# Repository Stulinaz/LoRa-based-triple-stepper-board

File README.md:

<!-- For .md file development refers to https://docs.github.com/en -->
# LoRa Wireless Triple Stepper Controller 

## Build for 7th PCBWAy Project Design Contest

[CLICK HERE](https://www.pcbway.com/project/shareproject/LoRa_based_triple_stepper_board_7cf3be2c.html) to see the project.

Designed to remote control up to three axis mechatronic system.
Build with [MIPOT](https://www.mipot.com) [32001506DEU](https://mipot.com/en/products/mip-series/dual-core/32001506deu/) LoRa Open Core module based on 
[STM32WL55JC](https://www.st.com/en/microcontrollers-microprocessors/stm32wl55cc.html) dual core microcontroller.

## Top Side of the board

## Bottom Side of The board

## Board with 4 layers for EMI Compliance

## Build with Kicad

## Main firwmare files for a quick view

## Pcb and stencil order on pcbway

## Mode of Operation

## Closeup

## SPI commonucation between microcontroller and TMC2130 Drivers

## Electrical characteristics

| Parameter                | Description | Min        | Typ     | Max     |  Unit  | Test Conditions         |    
| ---                      |    ---      | ---        | ---     | ---     | ---    | ---                     |   
|**Input Voltage**         | -           | 6          |         | 45      | V      | -                       |   
|**Operating temperature** | -           | 0          | 25      | 55      | \*C    | -                       |
|**Power consumption**     | -           | -          | 47      | -       | mA     | Vcc 6Vdc - Steppers Off |

## Folder content and description

- **technical_docs:** Datasheet, Application notes and manual of the on-board electronic components.
- **firmware:** Source code of the microcontroller written in C.
	- **Core:** The application files, system and peripheral configuration.
	- **freertos:** The Freertos kernel. *Keep read only*.
	- **freertos_cli:** The Freertos command line interface source code. *Keep read only*.
	- **wl-lib:** STM32 HAL and LL Drivers. *Keep read only*.
	- **trinamic_lib:** Driver of TMC2130 stepper controller.
	- **miplib** Driver of MIPOT LoRa Module 32001506DEU. *Keep read only*.
- **img:** Development and test images of the project.
- **kicad:** hardware design files.Source files of schematic and PCB.
	- **lib:** Symbols and footprints of the components.
- **production:** Production files. Gerbers, BOM and Stencil.
- **doc:**  User manual of the board and Schematic. PDF format.

## Bll of materials

Interactive [BOM](https://github.com/Stulinaz/LoRa-based-triple-stepper-board/blob/master/production/ibom.html).

## Firmware characteristics

Based on [Freertos](https://www.freertos.org) with simple and clean development.
.

## Software needed for development

- [STM32CubeIDE](https://www.st.com/en/development-tools/stm32cubeide.html) **1.17.0**
- [KICAD](https://www.kicad.org/) **8.0.5**
- [GIT](https://git-scm.com/) **2.46.1.windows.1**
- [Tera Term](https://teratermproject.github.io/index-en.html) **5.3 x86**

## Tools needed for development

Programmer [STLINK](https://www.st.com/en/development-tools/st-link-v2.html).

## License

Shown in the LICENSE.md file

## Developers

Hardware developer: [@ts-manuel](https://github.com/ts-manuel)
Firmware developer: [@Stulinaz](https://github.com/Stulinaz)

> [!CAUTION]
> Manual soldering of SMD components requires high level of manual skills.
> Project not suited for beginners in firmware development.
> A good understanding of C language is a must.

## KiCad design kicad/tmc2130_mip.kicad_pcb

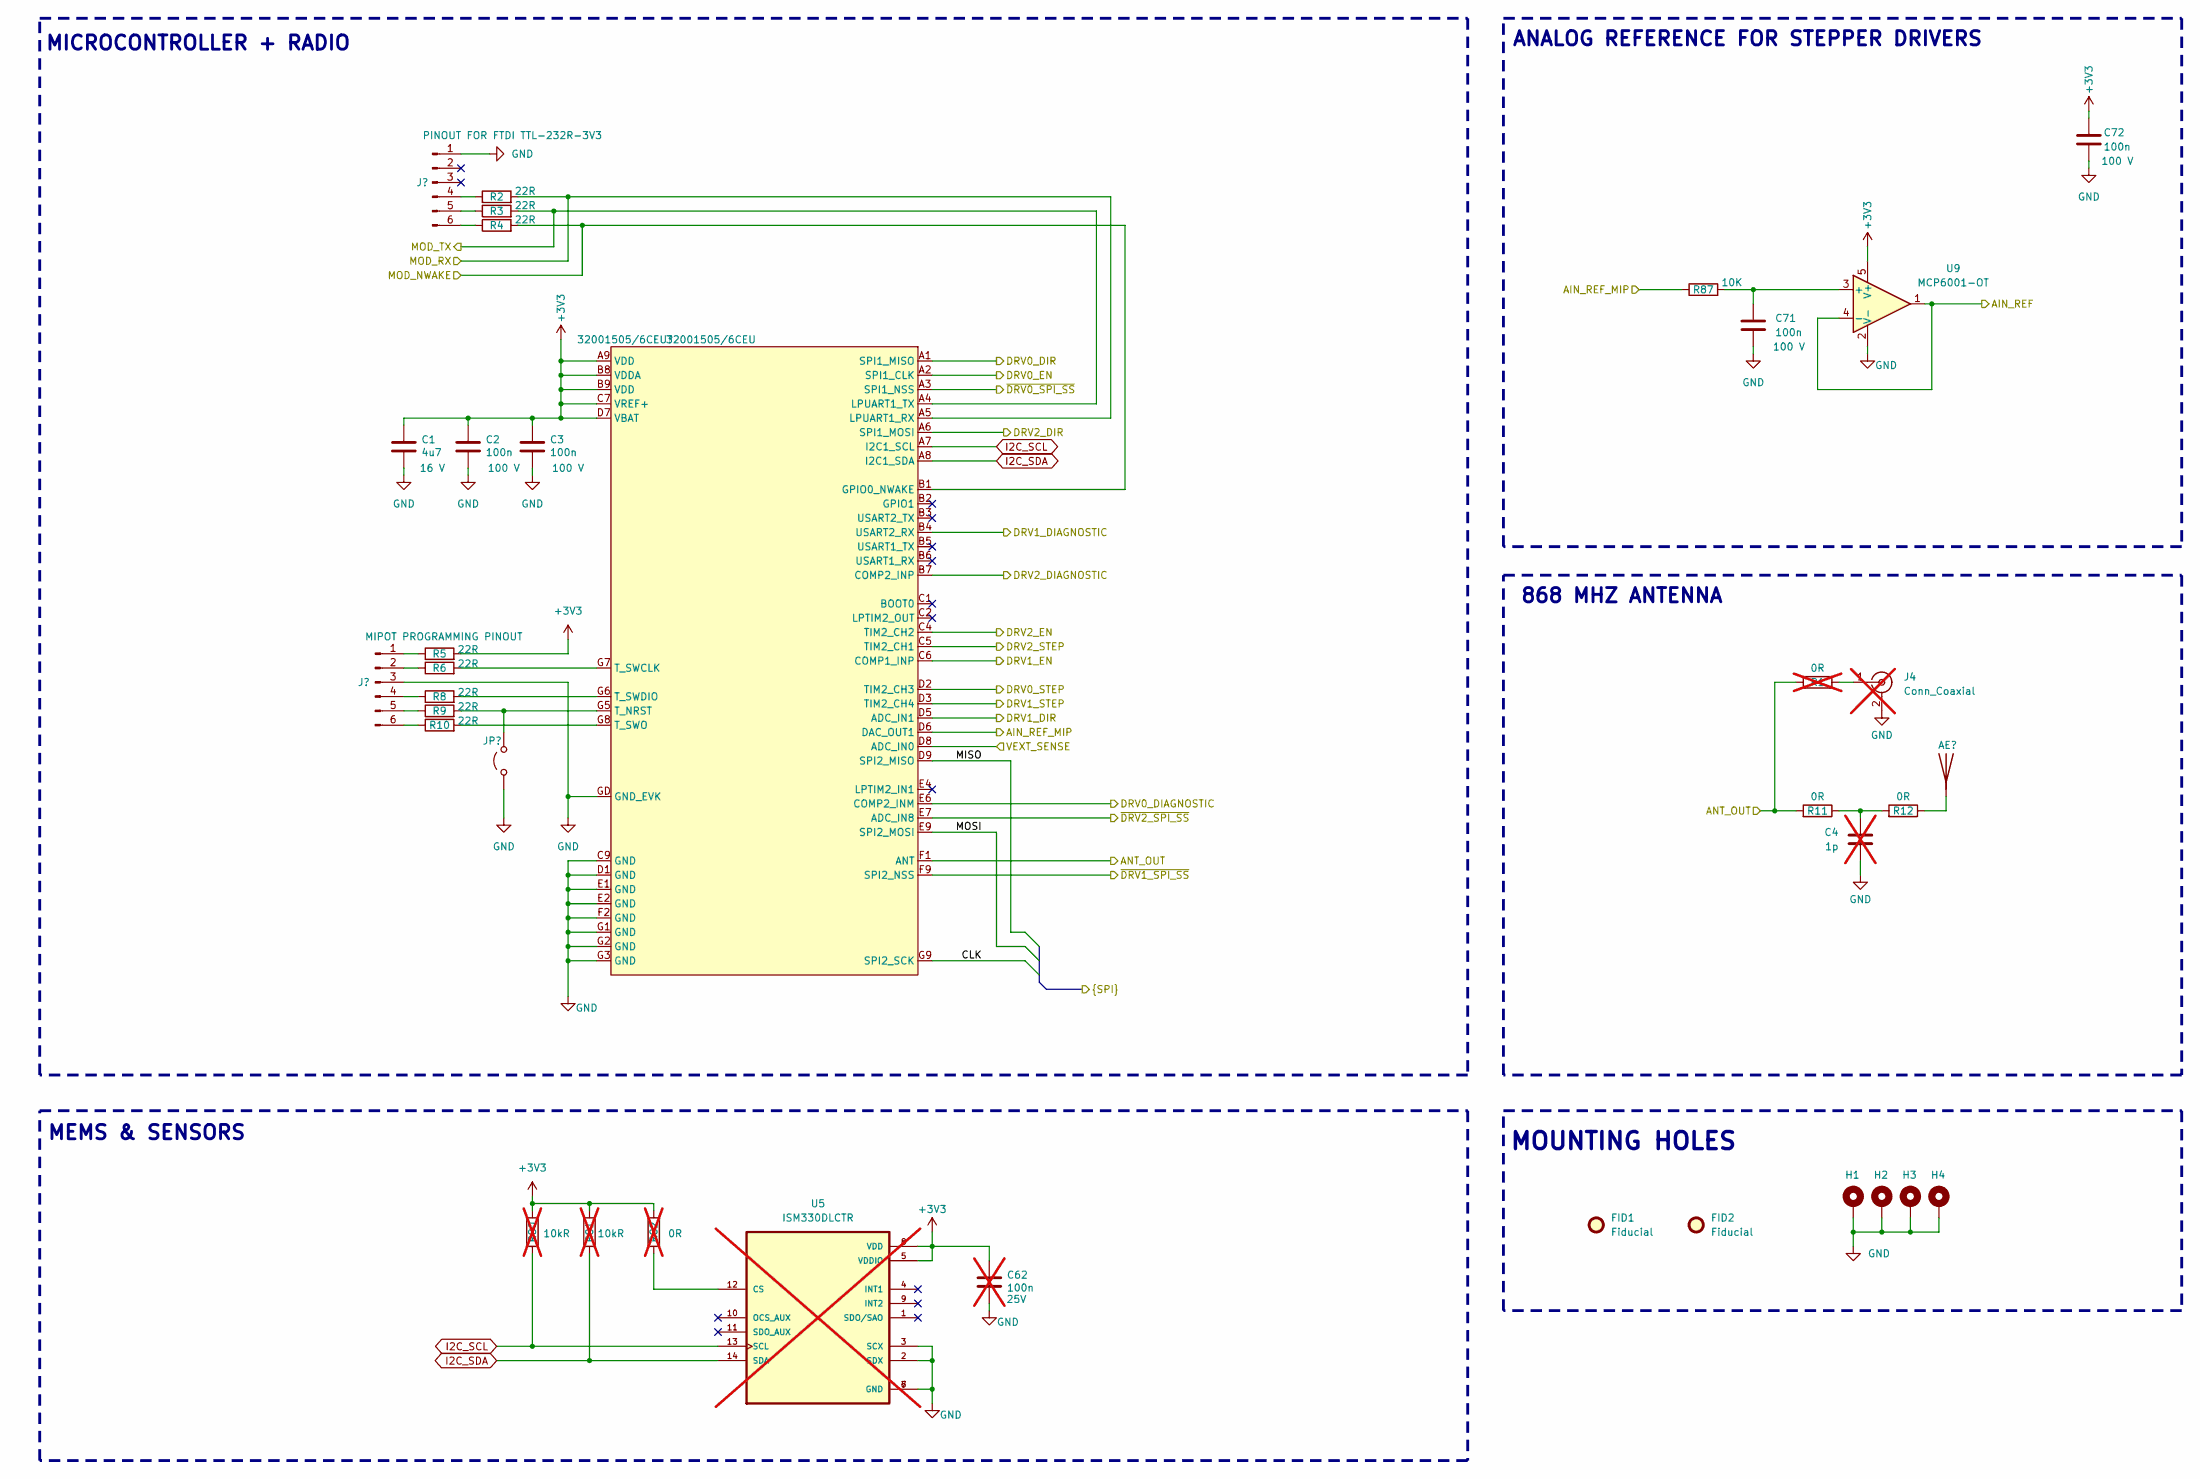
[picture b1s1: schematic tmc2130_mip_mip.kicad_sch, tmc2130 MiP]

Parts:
AE1: Antenna; Texas_SWRA416_868MHz_915MHz
C1: 4u7; C_0805_2012Metric_Pad1.18x1.45mm_HandSolder; Voltage 16 V; Mouser 81-GRM21BR71C475KE1L
C2, C3, C71, C72: 100n; C_0603_1608Metric_Pad1.08x0.95mm_HandSolder; Voltage 100 V; Mouser 187-CL10B104KC8NNNC
C4: 1p; C_0603_1608Metric_Pad1.08x0.95mm_HandSolder; not fitted
C62: 100n; C_0603_1608Metric_Pad1.08x0.95mm_HandSolder; not fitted
FID1, FID2: Fiducial; Fiducial_2.0mm_Mask4.0mm
H1, H2, H3, H4: MountingHole_Pad; MountingHole_4.3mm_M4_ISO7380_Pad_TopBottom
J1: Conn_01x06_Pin; PinSocket_1x06_P2.54mm_Vertical
J2: Conn_01x06_Pin; PinHeader_1x06_P2.54mm_Vertical
J4: Conn_Coaxial; U.FL_Molex_MCRF_73412-0110_Vertical; Mouser 538-73412-0110; not fitted
JP1: Jumper_2_Open; PinHeader_1x02_P2.54mm_Vertical
M1: 32001505/6CEU; 32001514_R2
R1, R82: 0R; R_0603_1608Metric_Pad0.98x0.95mm_HandSolder; not fitted
R2, R3, R4, R5, R6, R8, R9, R10: 22R; R_0603_1608Metric_Pad0.98x0.95mm_HandSolder; Mouser 603-AC0603JR-0722RL
R11, R12: 0R; R_0603_1608Metric_Pad0.98x0.95mm_HandSolder; Mouser 603-RC0603FR-100RL
R80, R81: 10kR; R_0603_1608Metric_Pad0.98x0.95mm_HandSolder; not fitted
R87: 10K; R_0603_1608Metric_Pad0.98x0.95mm_HandSolder; Mouser 603-RC0603JR-0710KL
U5: ISM330DLCTR; PQFN50P250X300X86-14N; PARTREV 2; not fitted
U9: MCP6001-OT; SOT-23-5; Mouser 579-MCP6001T-E/OT

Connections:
+3V3: C1.2, C2.2, C3.2, C62.2, C72.2, M1.A9 (VDD), M1.B8 (VDDA), M1.B9 (VDD), M1.C7 (VREF+), M1.D7 (VBAT), R5.2, R80.1, R81.1, R82.1, U5.5 (VDDIO), U5.8 (VDD), U9.5 (V+); also elsewhere on the board
/CPU/AIN_REF: U9.1, U9.4 (-); also elsewhere on the board
/CPU/AIN_REF_MIP: M1.D6 (DAC_OUT1), R87.1
/CPU/ANT_OUT: M1.F1 (ANT), R1.2, R11.2
/CPU/CLK: M1.G9 (SPI2_SCK); also elsewhere on the board
/CPU/DRV0_DIAGNOSTIC: M1.E6 (COMP2_INM); also elsewhere on the board
/CPU/DRV0_DIR: M1.A1 (SPI1_MISO); also elsewhere on the board
/CPU/DRV0_EN: M1.A2 (SPI1_CLK); also elsewhere on the board
/CPU/DRV0_STEP: M1.D2 (TIM2_CH3); also elsewhere on the board
/CPU/DRV1_DIAGNOSTIC: M1.B4 (USART2_RX); also elsewhere on the board
/CPU/DRV1_DIR: M1.D5 (ADC_IN1); also elsewhere on the board
/CPU/DRV1_EN: M1.C6 (COMP1_INP); also elsewhere on the board
/CPU/DRV1_STEP: M1.D3 (TIM2_CH4); also elsewhere on the board
/CPU/DRV2_DIAGNOSTIC: M1.B7 (COMP2_INP); also elsewhere on the board
/CPU/DRV2_DIR: M1.A6 (SPI1_MOSI); also elsewhere on the board
/CPU/DRV2_EN: M1.C4 (TIM2_CH2); also elsewhere on the board
/CPU/DRV2_STEP: M1.C5 (TIM2_CH1); also elsewhere on the board
/CPU/MISO: M1.D9 (SPI2_MISO); also elsewhere on the board
/CPU/MOD_NWAKE: M1.B1 (GPIO0_NWAKE), R4.2; also elsewhere on the board
/CPU/MOD_RX: M1.A5 (LPUART1_RX), R2.2; also elsewhere on the board
/CPU/MOD_TX: M1.A4 (LPUART1_TX), R3.2; also elsewhere on the board
/CPU/MOSI: M1.E9 (SPI2_MOSI); also elsewhere on the board
/CPU/VEXT_SENSE: M1.D8 (ADC_IN0); also elsewhere on the board
/CPU/~DRV0_SPI_SS: M1.A3 (SPI1_NSS); also elsewhere on the board
/CPU/~DRV1_SPI_SS: M1.F9 (SPI2_NSS); also elsewhere on the board
/CPU/~DRV2_SPI_SS: M1.E7 (ADC_IN8); also elsewhere on the board
GND: C1.1, C2.1, C3.1, C4.1, C62.1, C71.1, C72.1, H1.1, H2.1, H3.1, H4.1, J1.1, J2.3, J4.2 (Ext), JP1.1 (A), M1.C9 (GND), M1.D1 (GND), M1.E1 (GND), M1.E2 (GND), M1.F2 (GND), M1.G1 (GND), M1.G2 (GND), M1.G3 (GND), M1.GD (GND_EVK), U5.2 (SDX), U5.3 (SCX), U5.6 (GND), U5.7 (GND), U9.2 (V-); also elsewhere on the board
I2C_SCL: M1.A7 (I2C1_SCL), R80.2, U5.13 (SCL)
I2C_SDA: M1.A8 (I2C1_SDA), R81.2, U5.14 (SDA)
unnamed: AE1.1 (A), R12.1
unnamed: C4.2, R11.1, R12.2
unnamed: J1.4, R2.1
unnamed: J1.5, R3.1
unnamed: J1.6, R4.1
unnamed: J2.1, R5.1
unnamed: J2.2, R6.1
unnamed: J2.4, R8.1
unnamed: J2.5, R9.1
unnamed: J2.6, R10.1
unnamed: J4.1 (In), R1.1
unnamed: JP1.2 (B), M1.G5 (T_NRST), R9.2
unnamed: M1.G7 (T_SWCLK), R6.2
unnamed: M1.G6 (T_SWDIO), R8.2
unnamed: M1.G8 (T_SWO), R10.2
unnamed: R82.2, U5.12 (CS)
unnamed: C71.2, R87.2, U9.3 (+)

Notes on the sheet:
MEMS & SENSORS
MICROCONTROLLER + RADIO
MOUNTING HOLES
ANALOG REFERENCE FOR STEPPER DRIVERS
868 MHZ ANTENNA

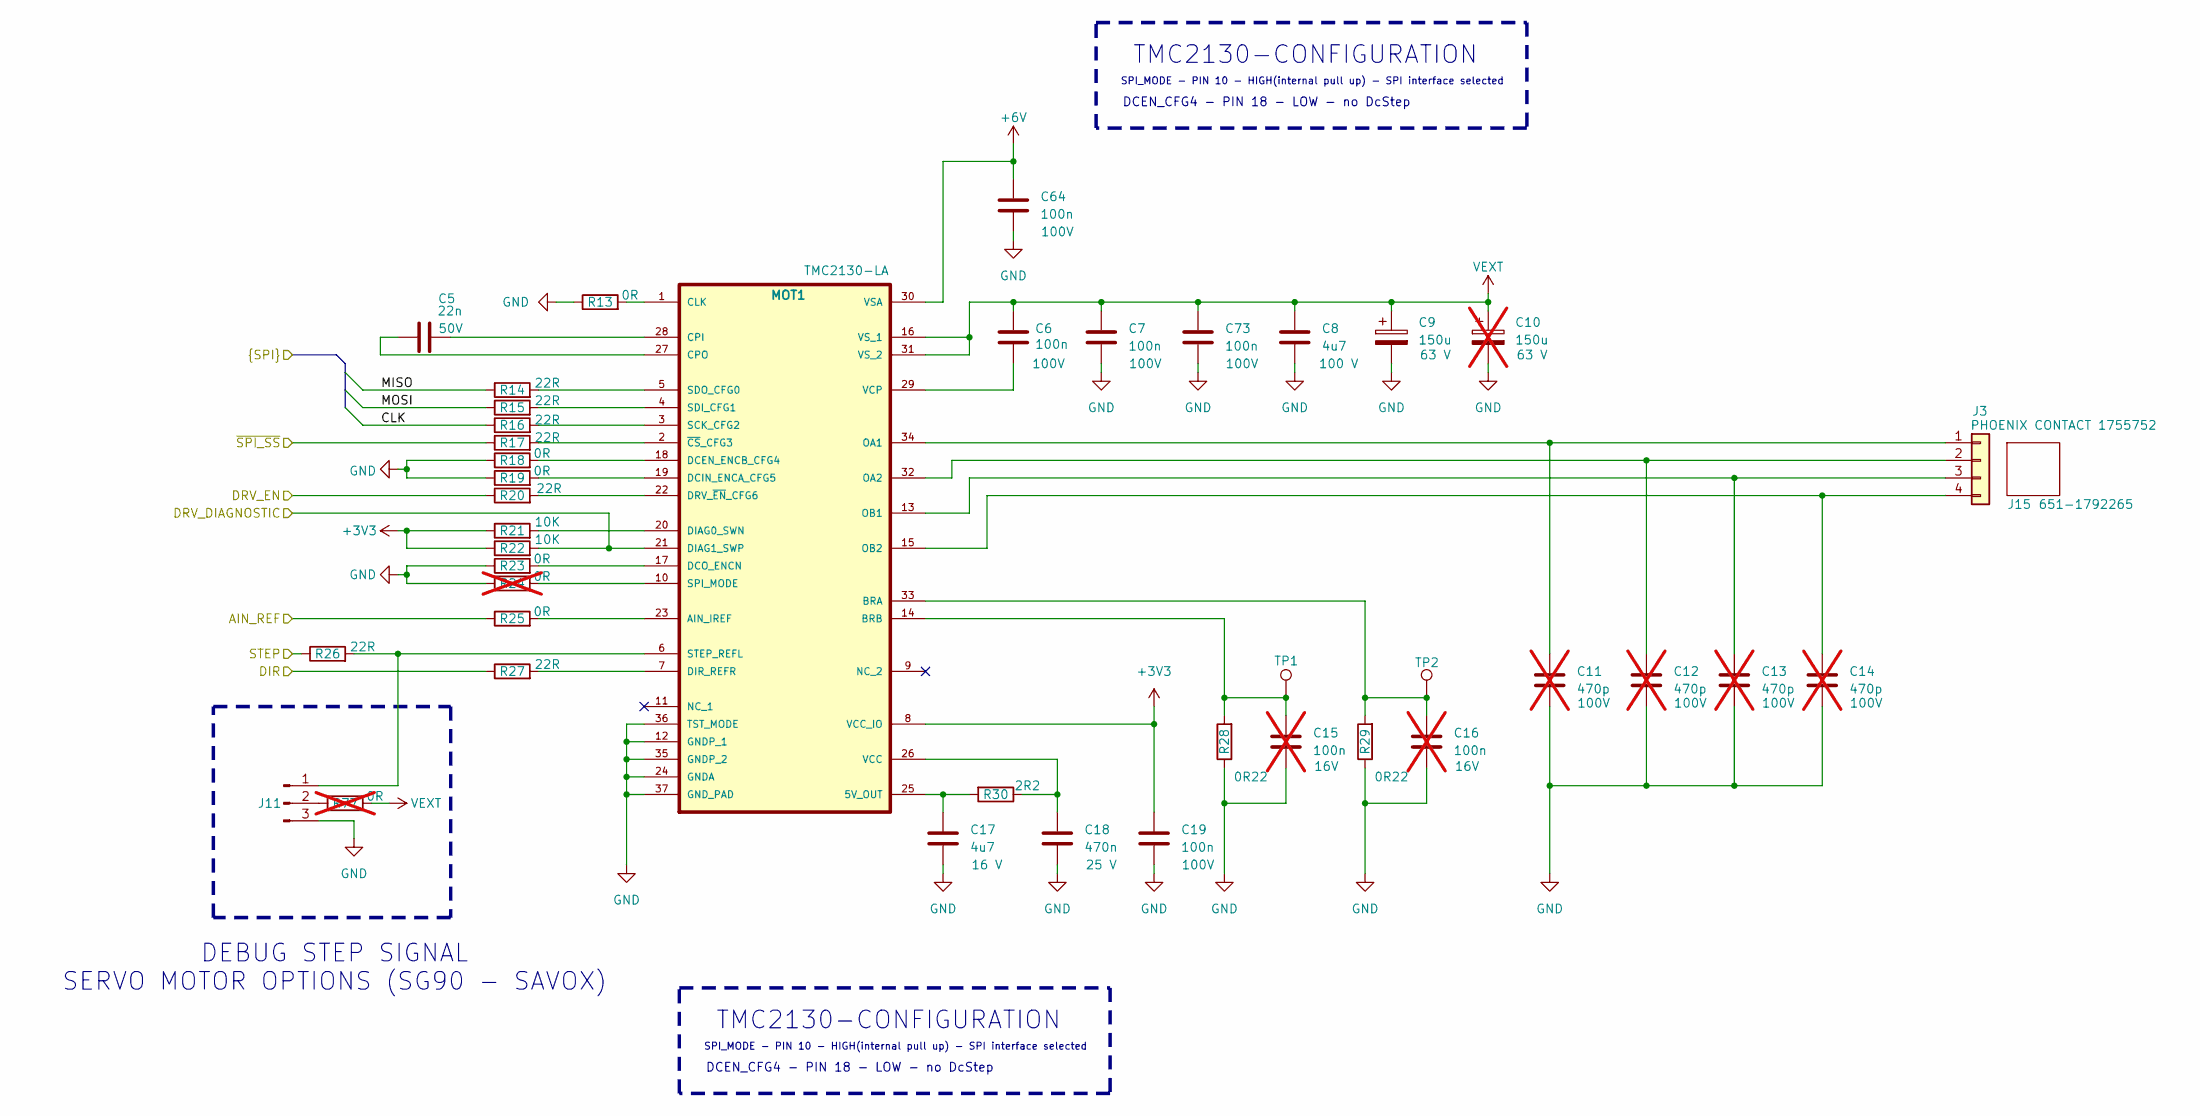
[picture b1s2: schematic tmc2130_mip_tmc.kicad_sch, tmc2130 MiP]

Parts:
C5: 22n; C_0603_1608Metric_Pad1.08x0.95mm_HandSolder; Voltage 50V; Mouser 810-C1608X7R1H223K
C6, C7, C19, C64, C73: 100n; C_0603_1608Metric_Pad1.08x0.95mm_HandSolder; Voltage 100V; Mouser 187-CL10B104KC8NNNC
C8: 4u7; C_1206_3216Metric_Pad1.33x1.80mm_HandSolder; Voltage 100 V; Mouser 81-GRM31CZ72A475K11L
C9: 150u; CP_Radial_D10.0mm_P5.00mm; Voltage 63 V; Mouser 667-EEU-FR1J151
C10: 150u; CP_Radial_D10.0mm_P5.00mm; Voltage 63 V; Mouser 667-EEU-FR1J151; not fitted
C11, C12, C13, C14: 470p; C_0603_1608Metric_Pad1.08x0.95mm_HandSolder; not fitted
C15, C16: 100n; C_0603_1608Metric_Pad1.08x0.95mm_HandSolder; Voltage 100 V; Mouser 187-CL10B104KC8NNNC; not fitted
C17: 4u7; C_0805_2012Metric_Pad1.18x1.45mm_HandSolder; Voltage 16 V; Mouser 81-GRM21BR71C475KE1L
C18: 470n; C_0603_1608Metric_Pad1.08x0.95mm_HandSolder; Voltage 25 V; Mouser 187-CL10B474KA8NNNC
J3: PHOENIX CONTACT 1755752; PHOENIX_1755752; Mouser 651-1755752
J11: Conn_01x03_Pin; PinHeader_1x03_P2.54mm_Vertical
J15: PHOENIX_MVSTBR 2,5 4-ST-5,08; Mouser 651-1792265
MOT1: TMC2130-LA; TMC_QFN36_0.5_5.0X6.0; Mouser 700-TMC2130LA
R13, R18, R19, R23, R25: 0R; R_0603_1608Metric_Pad0.98x0.95mm_HandSolder; Mouser 603-RC0603FR-100RL
R14, R15, R16, R17, R20, R26, R27: 22R; R_0603_1608Metric_Pad0.98x0.95mm_HandSolder; Mouser 603-AC0603JR-0722RL
R21, R22: 10K; R_0603_1608Metric_Pad0.98x0.95mm_HandSolder; Mouser 603-RC0603JR-0710KL
R24, R77: 0R; R_0603_1608Metric_Pad0.98x0.95mm_HandSolder; not fitted
R28, R29: 0R22; R_1206_3216Metric_Pad1.30x1.75mm_HandSolder; Mouser 603-RL1206FR070R22L
R30: 2R2; R_0603_1608Metric_Pad0.98x0.95mm_HandSolder; Mouser 603-RC0603JR-072R2L
TP1, TP2: TestPoint; TestPoint_Pad_D1.0mm

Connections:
+3V3: C19.2, MOT1.8 (VCC_IO), R21.1, R22.1; also elsewhere on the board
+6V: C64.2, MOT1.30 (VSA); also elsewhere on the board
/CPU/AIN_REF: R25.1; also elsewhere on the board
/CPU/CLK: R16.1; also elsewhere on the board
/CPU/DRV0_DIAGNOSTIC: MOT1.21 (DIAG1_SWP), R22.2; also elsewhere on the board
/CPU/DRV0_DIR: R27.1; also elsewhere on the board
/CPU/DRV0_EN: R20.1; also elsewhere on the board
/CPU/DRV0_STEP: R26.1; also elsewhere on the board
/CPU/MISO: R14.1; also elsewhere on the board
/CPU/MOSI: R15.1; also elsewhere on the board
/CPU/~DRV0_SPI_SS: R17.1; also elsewhere on the board
GND: C7.1, C8.1, C9.2, C10.2, C11.2, C12.2, C13.2, C14.2, C15.1, C16.1, C17.1, C18.1, C19.1, C64.1, C73.1, J11.3, MOT1.12 (GNDP_1), MOT1.24 (GNDA), MOT1.35 (GNDP_2), MOT1.36 (TST_MODE), MOT1.37 (GND_PAD), R13.1, R18.1, R19.1, R23.1, R24.1, R28.1, R29.1; also elsewhere on the board
unnamed: C11.1, J3.1, MOT1.34 (OA1)
unnamed: C12.1, J3.2, MOT1.32 (OA2)
unnamed: C13.1, J3.3, MOT1.13 (OB1)
unnamed: C14.1, J3.4, MOT1.15 (OB2)
unnamed: J11.1, MOT1.6 (STEP_REFL), R26.2
unnamed: J11.2, R77.1
unnamed: C17.2, MOT1.25 (5V_OUT), R30.2
unnamed: MOT1.23 (AIN_IREF), R25.2
unnamed: C16.2, MOT1.33 (BRA), R29.2, TP2.1
unnamed: C15.2, MOT1.14 (BRB), R28.2, TP1.1
unnamed: MOT1.1 (CLK), R13.2
unnamed: C5.1, MOT1.28 (CPI)
unnamed: C5.2, MOT1.27 (CPO)
unnamed: MOT1.18 (DCEN_ENCB_CFG4), R18.2
unnamed: MOT1.19 (DCIN_ENCA_CFG5), R19.2
unnamed: MOT1.17 (DCO_ENCN), R23.2
unnamed: MOT1.20 (DIAG0_SWN), R21.2
unnamed: MOT1.7 (DIR_REFR), R27.2
unnamed: MOT1.22 (DRV_~EN_CFG6), R20.2
unnamed: MOT1.3 (SCK_CFG2), R16.2
unnamed: MOT1.4 (SDI_CFG1), R15.2
unnamed: MOT1.5 (SDO_CFG0), R14.2
unnamed: MOT1.10 (SPI_MODE), R24.2
unnamed: C18.2, MOT1.26 (VCC), R30.1
unnamed: C6.1, MOT1.29 (VCP)
unnamed: MOT1.2 (~CS_CFG3), R17.2
VEXT: C6.2, C7.2, C8.2, C9.1, C10.1, C73.2, MOT1.16 (VS_1), MOT1.31 (VS_2), R77.2; also elsewhere on the board

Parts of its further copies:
C20, C35: 22n; C_0603_1608Metric_Pad1.08x0.95mm_HandSolder; Voltage 50V; Mouser 810-C1608X7R1H223K
C21, C22, C34, C36, C37, C49, C68, C69, C74, C75: 100n; C_0603_1608Metric_Pad1.08x0.95mm_HandSolder; Voltage 100V; Mouser 187-CL10B104KC8NNNC
C23, C38: 4u7; C_1206_3216Metric_Pad1.33x1.80mm_HandSolder; Voltage 100 V; Mouser 81-GRM31CZ72A475K11L
C24, C39: 150u; CP_Radial_D10.0mm_P5.00mm; Voltage 63 V; Mouser 667-EEU-FR1J151
C25, C40: 150u; CP_Radial_D10.0mm_P5.00mm; Voltage 63 V; Mouser 667-EEU-FR1J151; not fitted
C26, C27, C28, C29, C41, C42, C43, C44: 470p; C_0603_1608Metric_Pad1.08x0.95mm_HandSolder; not fitted
C30, C31, C45, C46: 100n; C_0603_1608Metric_Pad1.08x0.95mm_HandSolder; Voltage 100 V; Mouser 187-CL10B104KC8NNNC; not fitted
C32, C47: 4u7; C_0805_2012Metric_Pad1.18x1.45mm_HandSolder; Voltage 16 V; Mouser 81-GRM21BR71C475KE1L
C33, C48: 470n; C_0603_1608Metric_Pad1.08x0.95mm_HandSolder; Voltage 25 V; Mouser 187-CL10B474KA8NNNC
J5, J7: PHOENIX CONTACT 1755752; PHOENIX_1755752; Mouser 651-1755752
J12, J13: Conn_01x03_Pin; PinHeader_1x03_P2.54mm_Vertical
J16, J17: PHOENIX_MVSTBR 2,5 4-ST-5,08; Mouser 651-1792265
MOT2, MOT3: TMC2130-LA; TMC_QFN36_0.5_5.0X6.0; Mouser 700-TMC2130LA
R31, R36, R37, R41, R43, R49, R54, R55, R59, R61: 0R; R_0603_1608Metric_Pad0.98x0.95mm_HandSolder; Mouser 603-RC0603FR-100RL
R32, R33, R34, R35, R38, R44, R45, R50, R51, R52, R53, R56, R62, R63: 22R; R_0603_1608Metric_Pad0.98x0.95mm_HandSolder; Mouser 603-AC0603JR-0722RL
R39, R40, R57, R58: 10K; R_0603_1608Metric_Pad0.98x0.95mm_HandSolder; Mouser 603-RC0603JR-0710KL
R42, R60, R78, R79: 0R; R_0603_1608Metric_Pad0.98x0.95mm_HandSolder; not fitted
R46, R47, R64, R65: 0R22; R_1206_3216Metric_Pad1.30x1.75mm_HandSolder; Mouser 603-RL1206FR070R22L
R48, R66: 2R2; R_0603_1608Metric_Pad0.98x0.95mm_HandSolder; Mouser 603-RC0603JR-072R2L
TP3, TP4, TP5, TP6: TestPoint; TestPoint_Pad_D1.0mm

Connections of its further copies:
+3V3: C34.2, C49.2, MOT2.8 (VCC_IO), MOT3.8 (VCC_IO), R39.1, R40.1, R57.1, R58.1; also elsewhere on the board
+6V: C68.2, C69.2, MOT2.30 (VSA), MOT3.30 (VSA); also elsewhere on the board
/CPU/AIN_REF: R43.1, R61.1; also elsewhere on the board
/CPU/CLK: R34.1, R52.1; also elsewhere on the board
/CPU/DRV1_DIAGNOSTIC: MOT2.21 (DIAG1_SWP), R40.2; also elsewhere on the board
/CPU/DRV1_DIR: R45.1; also elsewhere on the board
/CPU/DRV1_EN: R38.1; also elsewhere on the board
/CPU/DRV1_STEP: R44.1; also elsewhere on the board
/CPU/DRV2_DIAGNOSTIC: MOT3.21 (DIAG1_SWP), R58.2; also elsewhere on the board
/CPU/DRV2_DIR: R63.1; also elsewhere on the board
/CPU/DRV2_EN: R56.1; also elsewhere on the board
/CPU/DRV2_STEP: R62.1; also elsewhere on the board
/CPU/MISO: R32.1, R50.1; also elsewhere on the board
/CPU/MOSI: R33.1, R51.1; also elsewhere on the board
/CPU/~DRV1_SPI_SS: R35.1; also elsewhere on the board
/CPU/~DRV2_SPI_SS: R53.1; also elsewhere on the board
GND: C22.1, C23.1, C24.2, C25.2, C26.2, C27.2, C28.2, C29.2, C30.1, C31.1, C32.1, C33.1, C34.1, C37.1, C38.1, C39.2, C40.2, C41.2, C42.2, C43.2, C44.2, C45.1, C46.1, C47.1, C48.1, C49.1, C68.1, C69.1, C74.1, C75.1, J12.3, J13.3, MOT2.12 (GNDP_1), MOT2.24 (GNDA), MOT2.35 (GNDP_2), MOT2.36 (TST_MODE), MOT2.37 (GND_PAD), MOT3.12 (GNDP_1), MOT3.24 (GNDA), MOT3.35 (GNDP_2), MOT3.36 (TST_MODE), MOT3.37 (GND_PAD), R31.1, R36.1, R37.1, R41.1, R42.1, R46.1, R47.1, R49.1, R54.1, R55.1, R59.1, R60.1, R64.1, R65.1; also elsewhere on the board
unnamed: C26.1, J5.1, MOT2.34 (OA1)
unnamed: C27.1, J5.2, MOT2.32 (OA2)
unnamed: C28.1, J5.3, MOT2.13 (OB1)
unnamed: C29.1, J5.4, MOT2.15 (OB2)
unnamed: C41.1, J7.1, MOT3.34 (OA1)
unnamed: C42.1, J7.2, MOT3.32 (OA2)
unnamed: C43.1, J7.3, MOT3.13 (OB1)
unnamed: C44.1, J7.4, MOT3.15 (OB2)
unnamed: J12.1, MOT2.6 (STEP_REFL), R44.2
unnamed: J12.2, R78.1
unnamed: J13.1, MOT3.6 (STEP_REFL), R62.2
unnamed: J13.2, R79.1
unnamed: C32.2, MOT2.25 (5V_OUT), R48.2
unnamed: MOT2.23 (AIN_IREF), R43.2
unnamed: C31.2, MOT2.33 (BRA), R47.2, TP4.1
unnamed: C30.2, MOT2.14 (BRB), R46.2, TP3.1
unnamed: MOT2.1 (CLK), R31.2
unnamed: C20.1, MOT2.28 (CPI)
unnamed: C20.2, MOT2.27 (CPO)
unnamed: MOT2.18 (DCEN_ENCB_CFG4), R36.2
unnamed: MOT2.19 (DCIN_ENCA_CFG5), R37.2
unnamed: MOT2.17 (DCO_ENCN), R41.2
unnamed: MOT2.20 (DIAG0_SWN), R39.2
unnamed: MOT2.7 (DIR_REFR), R45.2
unnamed: MOT2.22 (DRV_~EN_CFG6), R38.2
unnamed: MOT2.3 (SCK_CFG2), R34.2
unnamed: MOT2.4 (SDI_CFG1), R33.2
unnamed: MOT2.5 (SDO_CFG0), R32.2
unnamed: MOT2.10 (SPI_MODE), R42.2
unnamed: C33.2, MOT2.26 (VCC), R48.1
unnamed: C21.1, MOT2.29 (VCP)
unnamed: MOT2.2 (~CS_CFG3), R35.2
unnamed: C47.2, MOT3.25 (5V_OUT), R66.2
unnamed: MOT3.23 (AIN_IREF), R61.2
unnamed: C46.2, MOT3.33 (BRA), R65.2, TP6.1
unnamed: C45.2, MOT3.14 (BRB), R64.2, TP5.1
unnamed: MOT3.1 (CLK), R49.2
unnamed: C35.1, MOT3.28 (CPI)
unnamed: C35.2, MOT3.27 (CPO)
unnamed: MOT3.18 (DCEN_ENCB_CFG4), R54.2
unnamed: MOT3.19 (DCIN_ENCA_CFG5), R55.2
unnamed: MOT3.17 (DCO_ENCN), R59.2
unnamed: MOT3.20 (DIAG0_SWN), R57.2
unnamed: MOT3.7 (DIR_REFR), R63.2
unnamed: MOT3.22 (DRV_~EN_CFG6), R56.2
unnamed: MOT3.3 (SCK_CFG2), R52.2
unnamed: MOT3.4 (SDI_CFG1), R51.2
unnamed: MOT3.5 (SDO_CFG0), R50.2
unnamed: MOT3.10 (SPI_MODE), R60.2
unnamed: C48.2, MOT3.26 (VCC), R66.1
unnamed: C36.1, MOT3.29 (VCP)
unnamed: MOT3.2 (~CS_CFG3), R53.2
VEXT: C21.2, C22.2, C23.2, C24.1, C25.1, C36.2, C37.2, C38.2, C39.1, C40.1, C74.2, C75.2, MOT2.16 (VS_1), MOT2.31 (VS_2), MOT3.16 (VS_1), MOT3.31 (VS_2), R78.2, R79.2; also elsewhere on the board

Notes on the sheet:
TMC2130-CONFIGURATION
DEBUG STEP SIGNAL SERVO MOTOR OPTIONS (SG90 - SAVOX)
SPI_MODE - PIN 10 - HIGH(internal pull up) - SPI interface selected
DCEN_CFG4 - PIN 18 - LOW - no DcStep

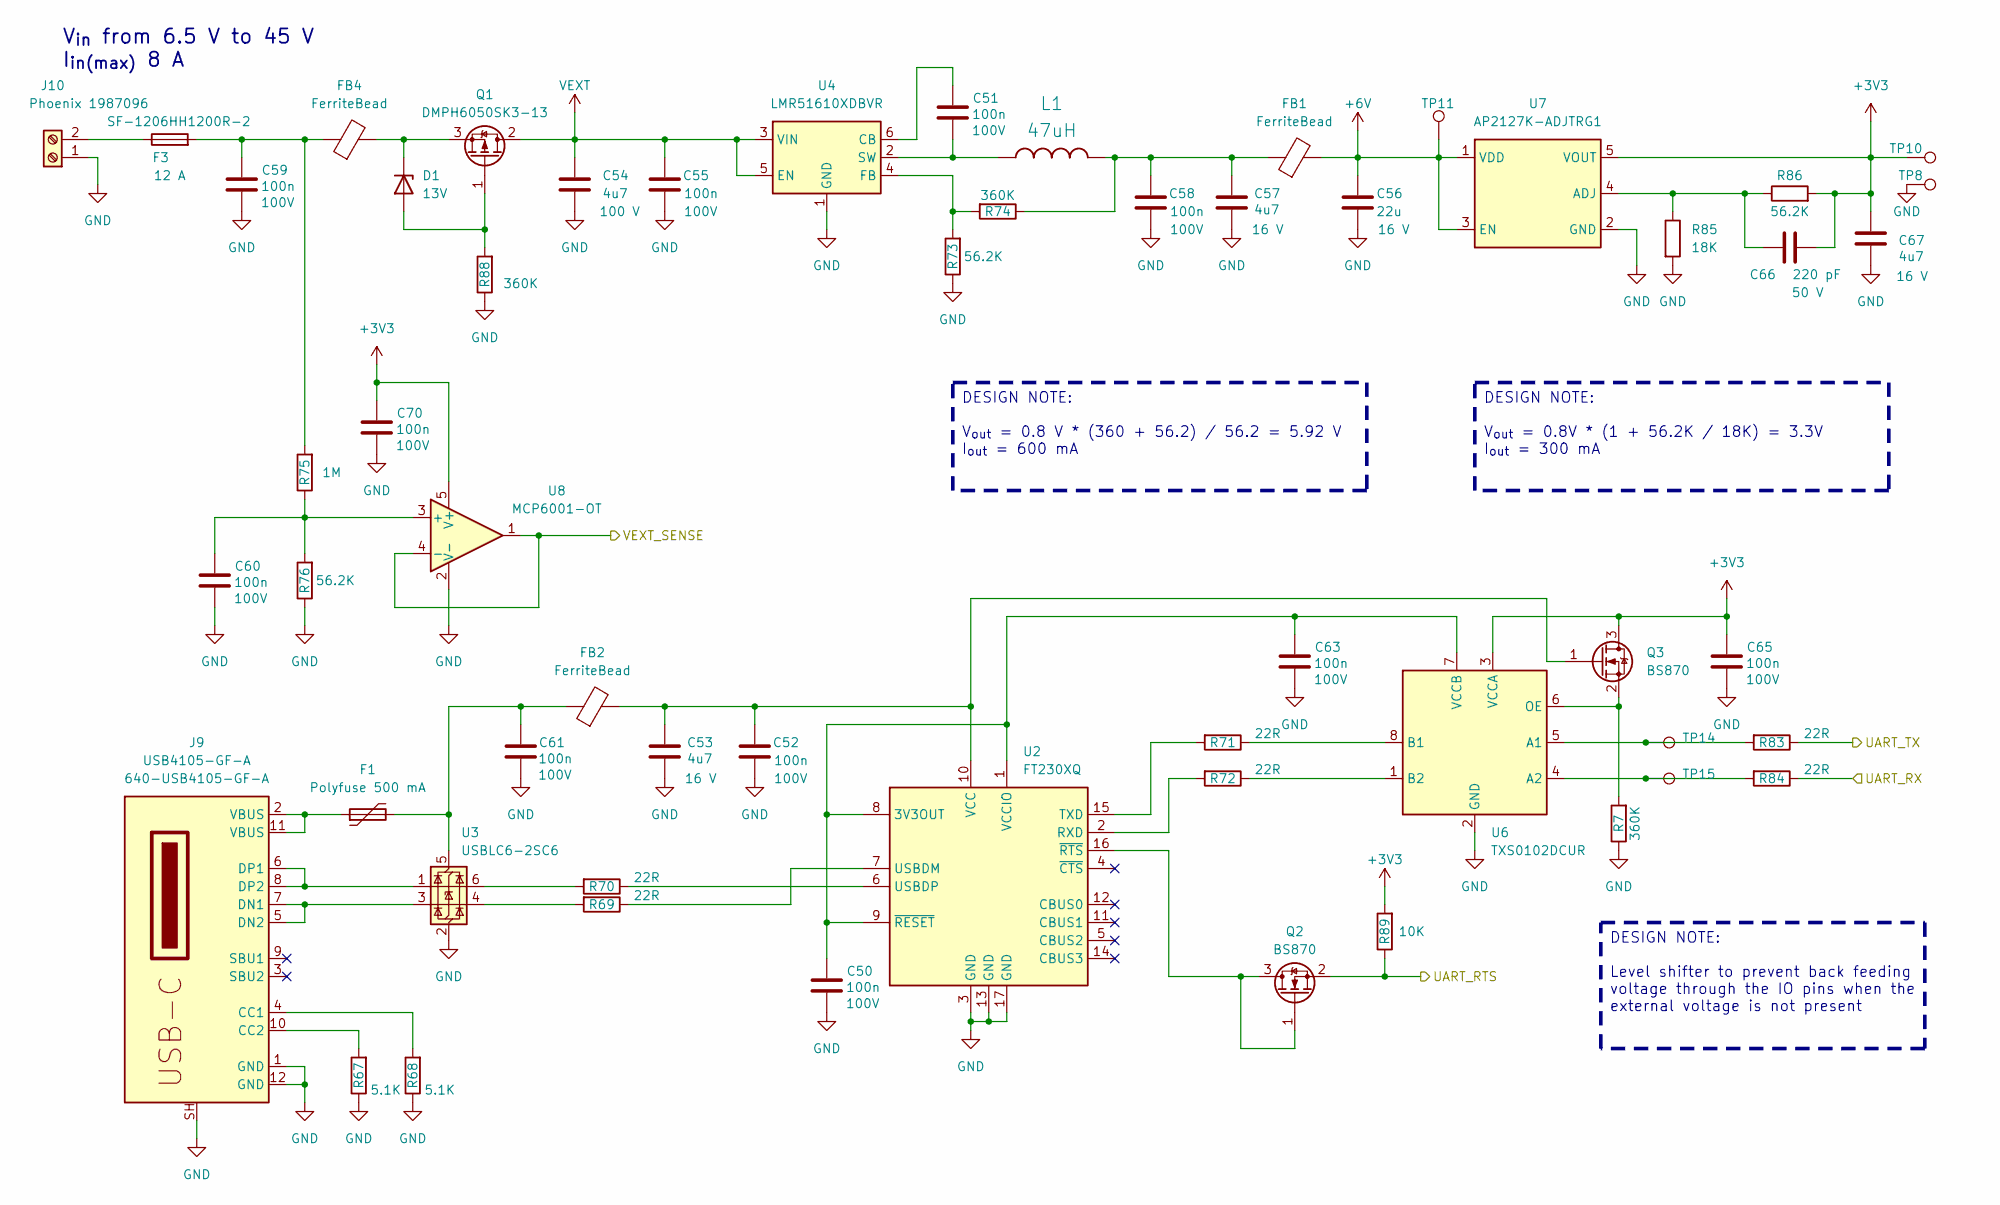
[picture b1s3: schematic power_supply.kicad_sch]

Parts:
C50, C51, C52, C55, C58, C59, C60, C61, C63, C65, C70: 100n; C_0603_1608Metric_Pad1.08x0.95mm_HandSolder; Voltage 100V; Mouser 187-CL10B104KC8NNNC
C53, C57, C67: 4u7; C_0805_2012Metric_Pad1.18x1.45mm_HandSolder; Voltage 16 V; Mouser 81-GRM21BR71C475KE1L
C54: 4u7; C_1206_3216Metric_Pad1.33x1.80mm_HandSolder; Voltage 100 V; Mouser 81-GRM31CZ72A475K11L
C56: 22u; C_1206_3216Metric_Pad1.33x1.80mm_HandSolder; Voltage 16 V; Mouser 187-CL31A226MOCLNNC
C66: 220 pF; C_0603_1608Metric_Pad1.08x0.95mm_HandSolder; Voltage 50 V; Mouser 80-C0603C221J5GAUTLR
D1: 13V; D_SOD-123; Mouser 771-BZT52-C13J
F1: Polyfuse 500 mA; Fuse_1210_3225Metric_Pad1.42x2.65mm_HandSolder; Mouser 650-MICROSMD050F-2
F3: 12 A; Fuse_1206_3216Metric_Pad1.42x1.75mm_HandSolder; Mouser SF-1206HH1200R-2
FB1, FB2, FB4: FerriteBead; Wurth_CBF_0805; Mouser 710-742792030
J9: USB4105-GF-A; USB-TYPE-C-12P; Mouser 640-USB4105-GF-A
J10: Phoenix 1987096; TerminalBlock_Phoenix_MKDS-1,5-2-5.08_1x02_P5.08mm_Horizont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; Mouser 651-1987096
L1: 47uH; L_Taiyo-Yuden_NR-60xx; Mouser 963-NRS6028T470MMGJ
Q1: DMPH6050SK3-13; TO-252-2; Mouser 621-DMPH6050SK3-13
Q2, Q3: BS870; SOT-23; Mouser 621-BS870-F
R7, R74, R88: 360K; R_0603_1608Metric_Pad0.98x0.95mm_HandSolder; Mouser 603-RT0603FRE07360KL
R67, R68: 5.1K; R_0603_1608Metric_Pad0.98x0.95mm_HandSolder; Mouser 603-RC0603FR-105K1L
R69, R70, R71, R72, R83, R84: 22R; R_0603_1608Metric_Pad0.98x0.95mm_HandSolder; Mouser 603-AC0603JR-0722RL
R73, R76, R86: 56.2K; R_0603_1608Metric_Pad0.98x0.95mm_HandSolder; Mouser 603-RC0402FR-0756K2L
R75: 1M; R_0603_1608Metric_Pad0.98x0.95mm_HandSolder; Mouser 603-RC0603FR-071ML
R85: 18K; R_0603_1608Metric_Pad0.98x0.95mm_HandSolder; Mouser 603-RC0402FR-0718KL
R89: 10K; R_0603_1608Metric_Pad0.98x0.95mm_HandSolder; Mouser 603-RC0603JR-0710KL
TP8, TP10, TP11, TP14, TP15: TestPoint_Pad_D1.0mm
U2: FT230XQ; QFN-16-1EP_4x4mm_P0.65mm_EP2.1x2.1mm; Mouser 895-FT230XQ-R
U3: USBLC6-2SC6; SOT-23-6; Mouser 511-USBLC6-2SC6
U4: LMR51610XDBVR; SOT-23-6; Mouser 595-LMR51610XDBVR
U6: TXS0102DCUR; VSSOP-8_2.3x2mm_P0.5mm; MPN TXS0102DCUR; LCSC C53434
U7: AP2127K-ADJTRG1; SOT-23-5; MPN AP2127K-ADJTRG1; LCSC C96343
U8: MCP6001-OT; SOT-23-5; Mouser 579-MCP6001T-E/OT

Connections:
+3V3: C65.1, C66.2, C67.2, C70.1, Q3.3 (D), R86.2, R89.2, TP10.1, U6.3 (VCCA), U7.5 (VOUT), U8.5 (V+); also elsewhere on the board
+6V: C56.2, FB1.2, TP11.1, U7.1 (VDD), U7.3 (EN); also elsewhere on the board
/CPU/MOD_NWAKE: Q2.2 (S), R89.1; also elsewhere on the board
/CPU/MOD_RX: R83.1; also elsewhere on the board
/CPU/MOD_TX: R84.1; also elsewhere on the board
/CPU/VEXT_SENSE: U8.1, U8.4 (-); also elsewhere on the board
GND: C50.2, C52.2, C53.1, C54.1, C55.2, C56.1, C57.1, C58.2, C59.2, C60.2, C61.2, C63.2, C65.2, C67.1, C70.2, J9.1 (GND), J9.12 (GND), J9.SH (SHIELD), J10.1, R7.1, R67.1, R68.1, R73.1, R76.1, R85.2, R88.1, TP8.1, U2.3 (GND), U2.13 (GND), U2.17 (GND), U3.2 (GND), U4.1 (GND), U6.2 (GND), U7.2 (GND), U8.2 (V-); also elsewhere on the board
unnamed: C57.2, C58.1, FB1.1, L1.2, R74.1
unnamed: C59.1, F3.2, FB4.1, R75.2
unnamed: D1.2 (A), Q1.1 (G), R88.2
unnamed: D1.1 (K), FB4.2, Q1.3 (S)
unnamed: F1.1, J9.2 (VBUS), J9.11 (VBUS)
unnamed: J9.4 (CC1), R68.2
unnamed: J9.10 (CC2), R67.2
unnamed: J9.5 (DN2), J9.7 (DN1), U3.3 (I/O2)
unnamed: J9.6 (DP1), J9.8 (DP2), U3.1 (I/O1)
unnamed: F3.1, J10.2
unnamed: Q2.1 (G), Q2.3 (D), U2.16 (~RTS)
unnamed: C52.1, C53.2, FB2.2, Q3.1 (G), U2.10 (VCC)
unnamed: Q3.2 (S), R7.2, U6.6 (OE)
unnamed: R69.2, U3.4 (I/O2)
unnamed: R70.2, U3.6 (I/O1)
unnamed: C50.1, C63.1, U2.1 (VCCIO), U2.8 (3V3OUT), U2.9 (~RESET), U6.7 (VCCB)
unnamed: R72.2, U2.2 (RXD)
unnamed: R71.2, U2.15 (TXD)
unnamed: R69.1, U2.7 (USBDM)
unnamed: R70.1, U2.6 (USBDP)
unnamed: C61.1, F1.2, FB2.1, U3.5 (VBUS)
unnamed: C51.1, U4.6 (CB)
unnamed: R73.2, R74.2, U4.4 (FB)
unnamed: C51.2, L1.1, U4.2 (SW)
unnamed: R83.2, TP14.1, U6.5 (A1)
unnamed: R84.2, TP15.1, U6.4 (A2)
unnamed: R71.1, U6.8 (B1)
unnamed: R72.1, U6.1 (B2)
unnamed: C66.1, R85.1, R86.1, U7.4 (ADJ)
unnamed: C60.1, R75.1, R76.2, U8.3 (+)
VEXT: C54.2, C55.1, Q1.2 (D), U4.3 (VIN), U4.5 (EN); also elsewhere on the board

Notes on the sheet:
DESIGN NOTE: Level shifter to prevent back feeding voltage through the IO pins when the external voltage is not present
DESIGN NOTE: V_{out} = 0.8 V * (360 + 56.2) / 56.2 = 5.92 V I_{out} = 600 mA
DESIGN NOTE: V_{out} = 0.8V * (1 + 56.2K / 18K) = 3.3V I_{out} = 300 mA
V_{in} from 6.5 V to 45 V I_{in(max)} 8 A
